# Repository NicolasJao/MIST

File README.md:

# MIST
4ES3 L02

Final project of SMRTTECH 4ES3 course.

A PCB project. Has an LED matrix that lights up in patterns based on music input from a microphone. Can make robot faces that makes expressions. Made with KiCad v9.0.

See /RESOURCES/IMAGES/3D VIEWER to see images of the PCB.
See /CODE to see the programming of the PCB.

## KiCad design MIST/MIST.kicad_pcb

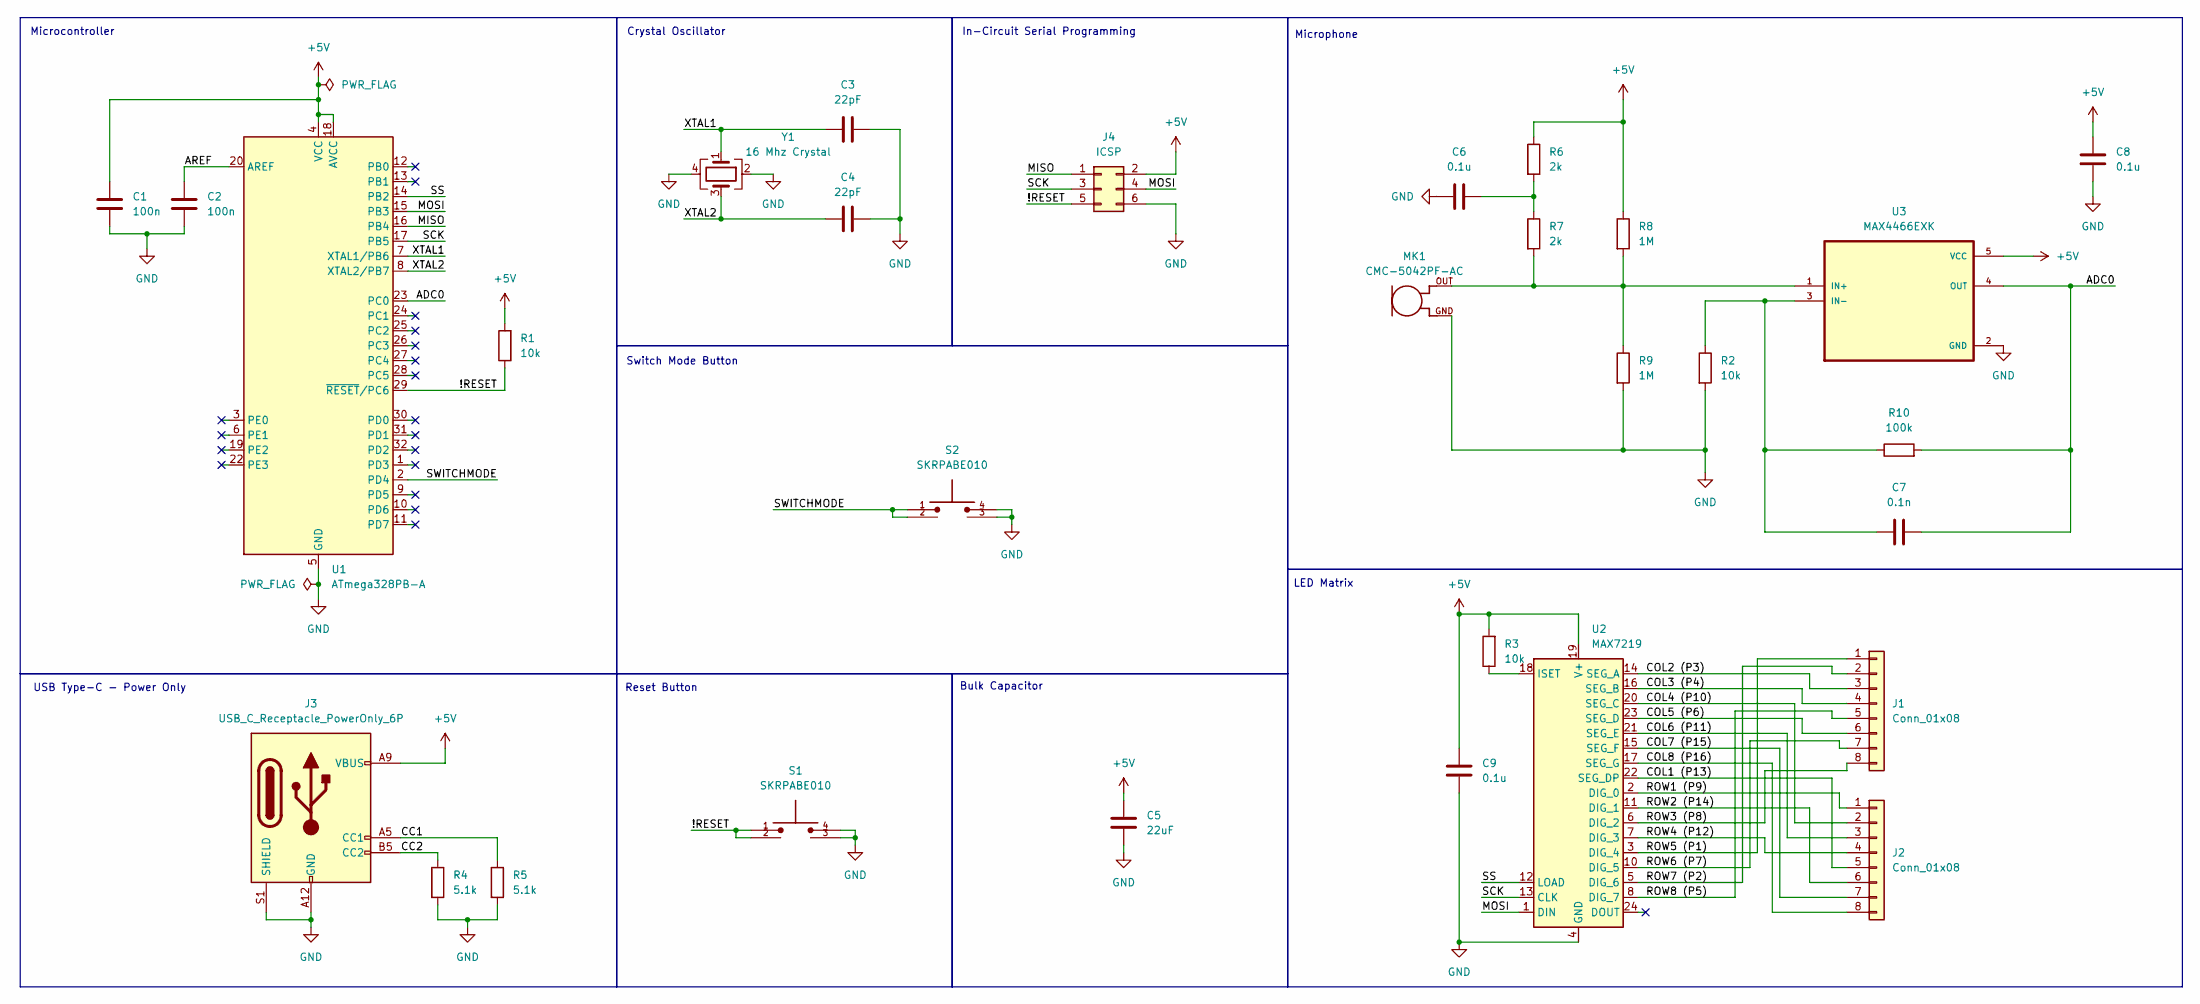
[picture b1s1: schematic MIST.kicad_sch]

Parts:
C1, C2: 100n; C_0805_2012Metric
C3, C4: 22pF; C_0805_2012Metric
C5: 22uF; C_0805_2012Metric
C6, C8, C9: 0.1u; C_0805_2012Metric
C7: 0.1n; C_0805_2012Metric
J1, J2: Conn_01x08; PinHeader_1x08_P2.54mm_Vertical
J3: USB_C_Receptacle_PowerOnly_6P; USB_C_Receptacle_GCT_USB4125-xx-x_6P_TopMnt_Horizontal
J4: ICSP; PinHeader_2x03_P2.54mm_Vertical
MK1: CMC-5042PF-AC; CUI_CMC-5042PF-AC
R1, R2: 10k; R_0805_2012Metric
R3: 10k; C_0805_2012Metric
R4, R5: 5.1k; C_0805_2012Metric
R6, R7: 2k; R_0805_2012Metric
R8, R9: 1M; R_0805_2012Metric
R10: 100k; R_0805_2012Metric
S1, S2: SKRPABE010; SW_SKRPABE010
U1: ATmega328PB-A; TQFP-32_7x7mm_P0.8mm
U2: MAX7219; SOIC-24W_7.5x15.4mm_P1.27mm
U3: MAX4466EXK; SOT65P210X110-5N
Y1: 16 Mhz Crystal; Crystal_SMD_3225-4Pin_3.2x2.5mm

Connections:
+5V: C1.2, C5.2, C8.1, C9.1, J3.A9 (VBUS), J3.B9 (VBUS), J4.2, R1.2, R3.2, R6.1, R8.1, U1.4 (VCC), U1.18 (AVCC), U2.19 (V+), U3.5 (VCC)
/!RESET: J4.5, R1.1, S1.1, S1.2, U1.29 (~RESET/PC6)
/ADC0: C7.2, R10.2, U1.23 (PC0), U3.4 (OUT)
/AREF: C2.2, U1.20 (AREF)
/CC1: J3.A5 (CC1), R5.1
/CC2: J3.B5 (CC2), R4.1
/COL1 (P13): J2.5, U2.22 (SEG_DP)
/COL2 (P3): J1.3, U2.14 (SEG_A)
/COL3 (P4): J1.4, U2.16 (SEG_B)
/COL4 (P10): J2.2, U2.20 (SEG_C)
/COL5 (P6): J1.6, U2.23 (SEG_D)
/COL6 (P11): J2.3, U2.21 (SEG_E)
/COL7 (P15): J2.7, U2.15 (SEG_F)
/COL8 (P16): J2.8, U2.17 (SEG_G)
/MISO: J4.1, U1.16 (PB4)
/MOSI: J4.4, U1.15 (PB3), U2.1 (DIN)
/ROW1 (P9): J2.1, U2.2 (DIG_0)
/ROW2 (P14): J2.6, U2.11 (DIG_1)
/ROW3 (P8): J1.8, U2.6 (DIG_2)
/ROW4 (P12): J2.4, U2.7 (DIG_3)
/ROW5 (P1): J1.1, U2.3 (DIG_4)
/ROW6 (P7): J1.7, U2.10 (DIG_5)
/ROW7 (P2): J1.2, U2.5 (DIG_6)
/ROW8 (P5): J1.5, U2.8 (DIG_7)
/SCK: J4.3, U1.17 (PB5), U2.13 (CLK)
/SS: U1.14 (PB2), U2.12 (LOAD)
/SWITCHMODE: S2.1, S2.2, U1.2 (PD4)
/XTAL1: C3.1, U1.7 (XTAL1/PB6), Y1.1
/XTAL2: C4.2, U1.8 (XTAL2/PB7), Y1.3
GND: C1.1, C2.1, C3.2, C4.1, C5.1, C6.1, C8.2, C9.2, J3.A12 (GND), J3.B12 (GND), J3.S1 (SHIELD), J4.6, MK1.GND, R2.2, R4.2, R5.2, R9.2, S1.3, S1.4, S2.3, S2.4, U1.5 (GND), U1.21 (GND), U2.4 (GND), U2.9 (GND), U3.2 (GND), Y1.2, Y1.4
unnamed: C6.2, R6.2, R7.1
unnamed: R3.1, U2.18 (ISET)
unnamed: MK1.OUT, R7.2, R8.2, R9.1, U3.1 (IN+)
unnamed: C7.1, R2.1, R10.1, U3.3 (IN-)

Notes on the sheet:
Bulk Capacitor
Switch Mode Button
LED Matrix
USB Type-C - Power Only
In-Circuit Serial Programming
Microcontroller
Reset Button
Crystal Oscillator
Microphone

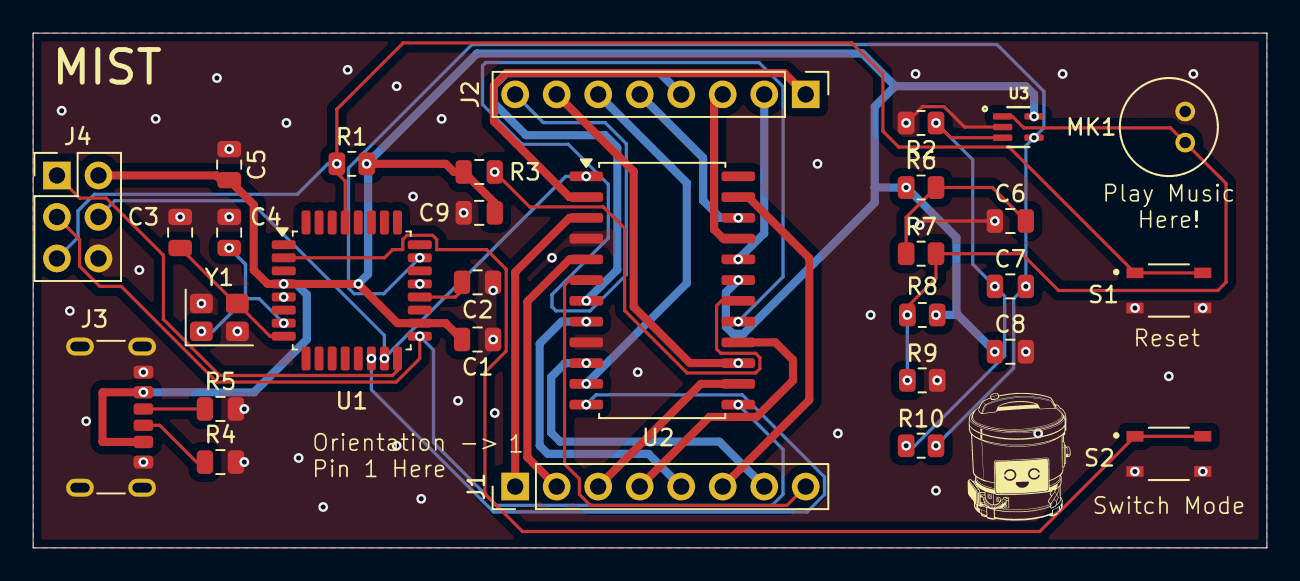
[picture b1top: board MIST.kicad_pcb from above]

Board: 2 copper layers, 75.5 x 31.5 mm, 30 parts (0 on the bottom side), 34 nets.

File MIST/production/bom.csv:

Designator,Footprint,Quantity,Value,LCSC Part #
"C1, C2",0805,2,100n,
"C3, C4",0805,2,22pF,
C5,0805,1,22uF,
"C6, C8, C9",0805,3,0.1u,
C7,0805,1,0.1n,
"J1, J2",PinHeader_1x08_P2.54mm_Vertical,2,Conn_01x08,
J3,USB_C_Receptacle_GCT_USB4125-xx-x_6P_TopMnt_Horizontal,1,USB_C_Receptacle_PowerOnly_6P,
J4,PinHeader_2x03_P2.54mm_Vertical,1,ICSP,
MK1,CUI_CMC-5042PF-AC,1,CMC-5042PF-AC,
"R1, R2, R3",0805,3,10k,
R10,0805,1,100k,
"R4, R5",0805,2,5.1k,
"R6, R7",0805,2,2k,
"R8, R9",0805,2,1M,
"S1, S2",SW_SKRPABE010,2,SKRPABE010,
U1,TQFP-32_7x7mm_P0.8mm,1,ATmega328PB-A,
U2,SOIC-24W_7.5x15.4mm_P1.27mm,1,MAX7219,
U3,SOT65P210X110-5N,1,MAX4466EXK,
Y1,Crystal_SMD_3225-4Pin_3.2x2.5mm,1,16 Mhz Crystal,

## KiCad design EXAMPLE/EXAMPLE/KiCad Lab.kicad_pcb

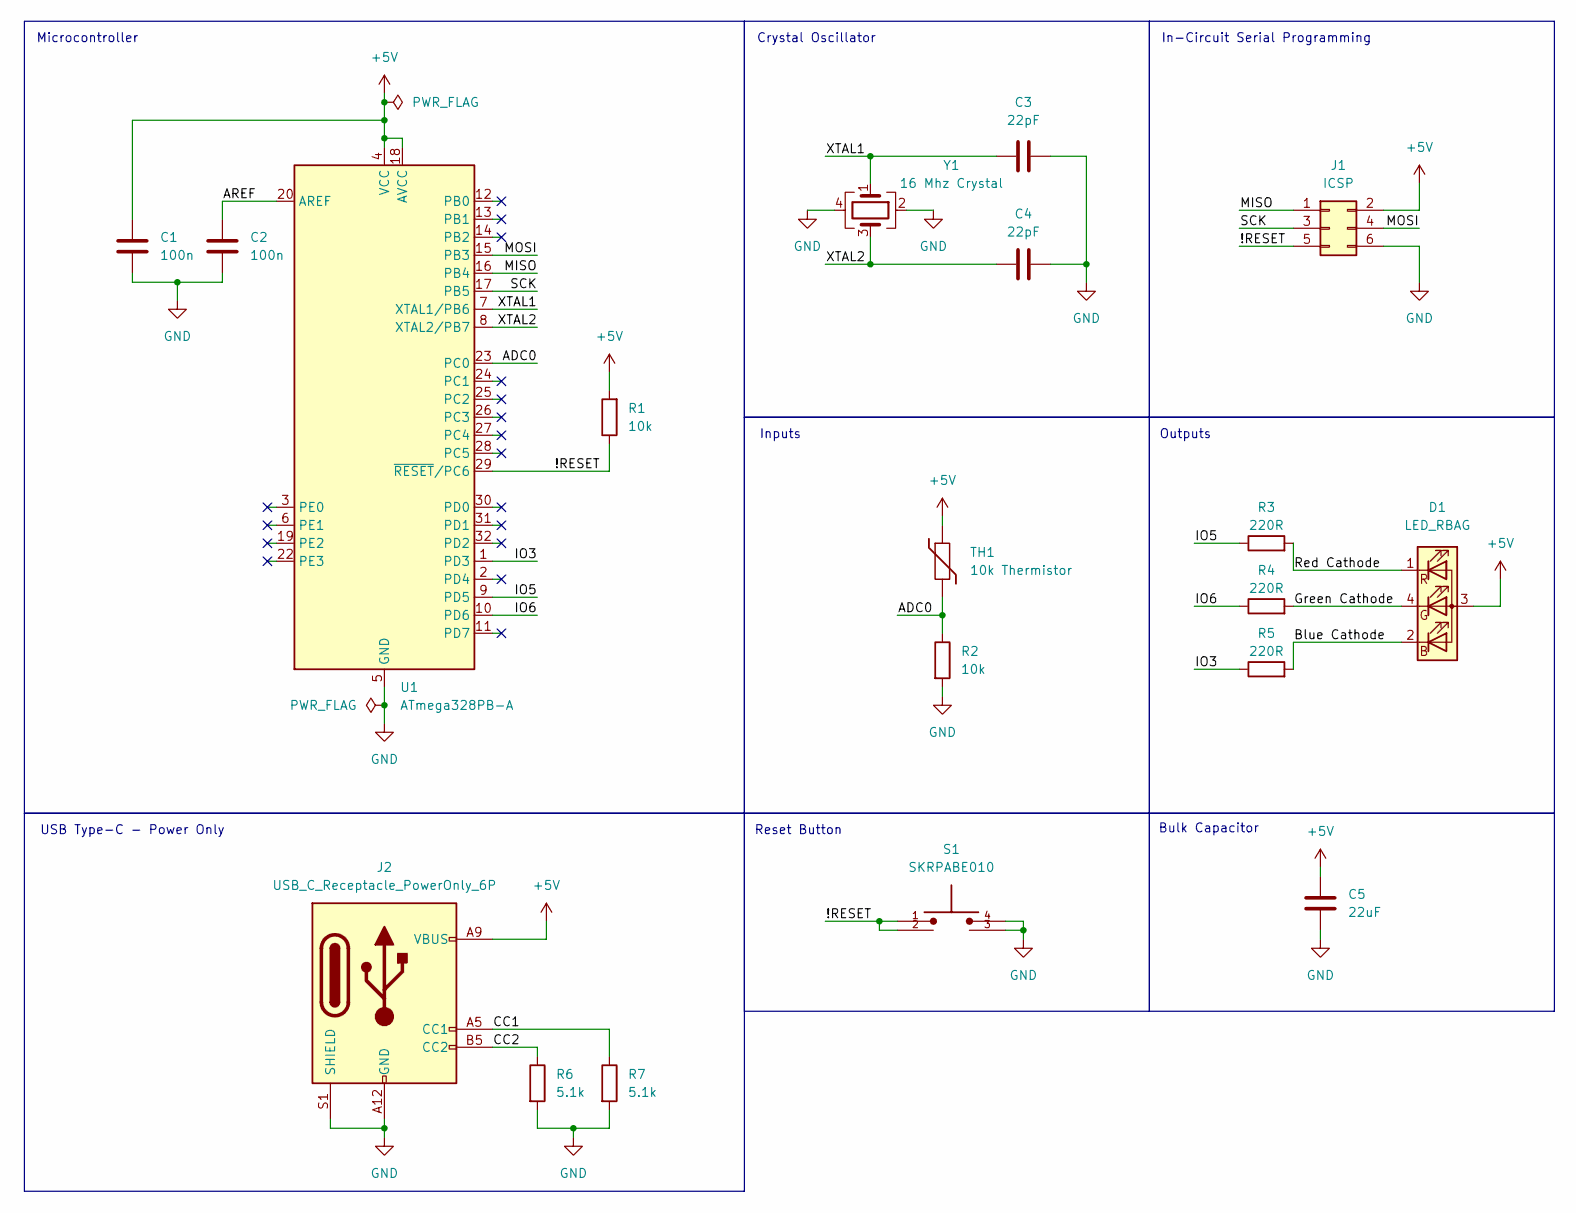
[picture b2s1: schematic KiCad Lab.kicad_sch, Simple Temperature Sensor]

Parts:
C1, C2: 100n; C_0805_2012Metric
C3, C4: 22pF; C_0805_2012Metric
C5: 22uF; C_0805_2012Metric
D1: LED_RBAG; LED_D5.0mm-4_RGB_Wide_Pins
J1: ICSP; PinHeader_2x03_P2.54mm_Vertical
J2: USB_C_Receptacle_PowerOnly_6P; USB_C_Receptacle_GCT_USB4125-xx-x_6P_TopMnt_Horizontal
R1, R2: 10k; R_1206_3216Metric
R3, R4, R5: 220R; R_1206_3216Metric
R6, R7: 5.1k; R_1206_3216Metric
S1: SKRPABE010; SW_SKRPABE010
TH1: 10k Thermistor; R_1206_3216Metric
U1: ATmega328PB-A; TQFP-32_7x7mm_P0.8mm
Y1: 16 Mhz Crystal; Crystal_SMD_3225-4Pin_3.2x2.5mm

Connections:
+5V: C1.2, C5.2, D1.3 (A), J1.2, J2.A9 (VBUS), J2.B9 (VBUS), R1.2, TH1.1, U1.4 (VCC), U1.18 (AVCC)
/!RESET: J1.5, R1.1, S1.1, S1.2, U1.29 (~RESET/PC6)
/ADC0: R2.1, TH1.2, U1.23 (PC0)
/AREF: C2.2, U1.20 (AREF)
/Blue Cathode: D1.2 (BK), R5.2
/CC1: J2.A5 (CC1), R7.1
/CC2: J2.B5 (CC2), R6.1
/Green Cathode: D1.4 (GK), R4.2
/IO3: R5.1, U1.1 (PD3)
/IO5: R3.1, U1.9 (PD5)
/IO6: R4.1, U1.10 (PD6)
/MISO: J1.1, U1.16 (PB4)
/MOSI: J1.4, U1.15 (PB3)
/Red Cathode: D1.1 (RK), R3.2
/SCK: J1.3, U1.17 (PB5)
/XTAL1: C3.1, U1.7 (XTAL1/PB6), Y1.1
/XTAL2: C4.2, U1.8 (XTAL2/PB7), Y1.3
GND: C1.1, C2.1, C3.2, C4.1, C5.1, J1.6, J2.A12 (GND), J2.B12 (GND), J2.S1 (SHIELD), R2.2, R6.2, R7.2, S1.3, S1.4, U1.5 (GND), U1.21 (GND), Y1.2, Y1.4

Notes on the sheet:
Inputs
In-Circuit Serial Programming
USB Type-C - Power Only
Microcontroller
Bulk Capacitor
Reset Button
Crystal Oscillator
Outputs

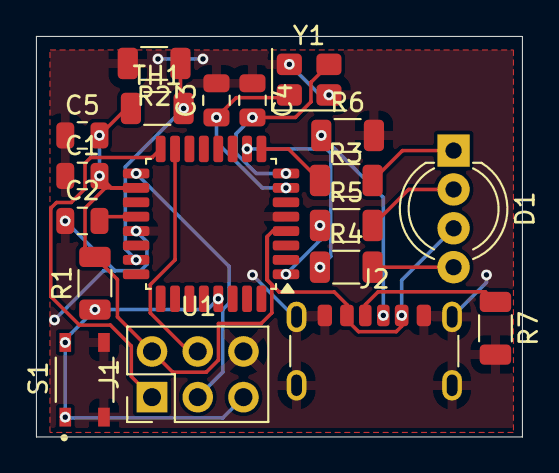
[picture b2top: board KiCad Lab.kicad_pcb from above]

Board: 2 copper layers, 27.0 x 22.2 mm, 19 parts (0 on the bottom side), 18 nets.

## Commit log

2026-03-08 did some stuff
2026-03-25 changed folder structure
2026-03-25 added a bunch of resources
2026-03-25 added README
2026-03-26 did stuff
2026-03-26 stuff
2026-03-29 finished BOM and added resources and started layout
2026-03-29 closed KiCad lol
2026-04-02 finished schematic. updated BOM. stuff.
2026-04-04 finished schematic and layout
2026-04-04 added GND planes to both layers and via stitched
2026-04-04 deleted 'how to import' html files lol
2026-04-04 edited README
2026-04-05 rearranged images folder
2026-04-05 added code folder
2026-04-20 fixed wrong matrix pin mappings schematic.
2026-04-20 fixed matrix pin mappings on layout. updated bitmap silkscreens.
